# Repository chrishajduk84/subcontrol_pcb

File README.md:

# subcontrol_pcb
PCB for the subcontrol project

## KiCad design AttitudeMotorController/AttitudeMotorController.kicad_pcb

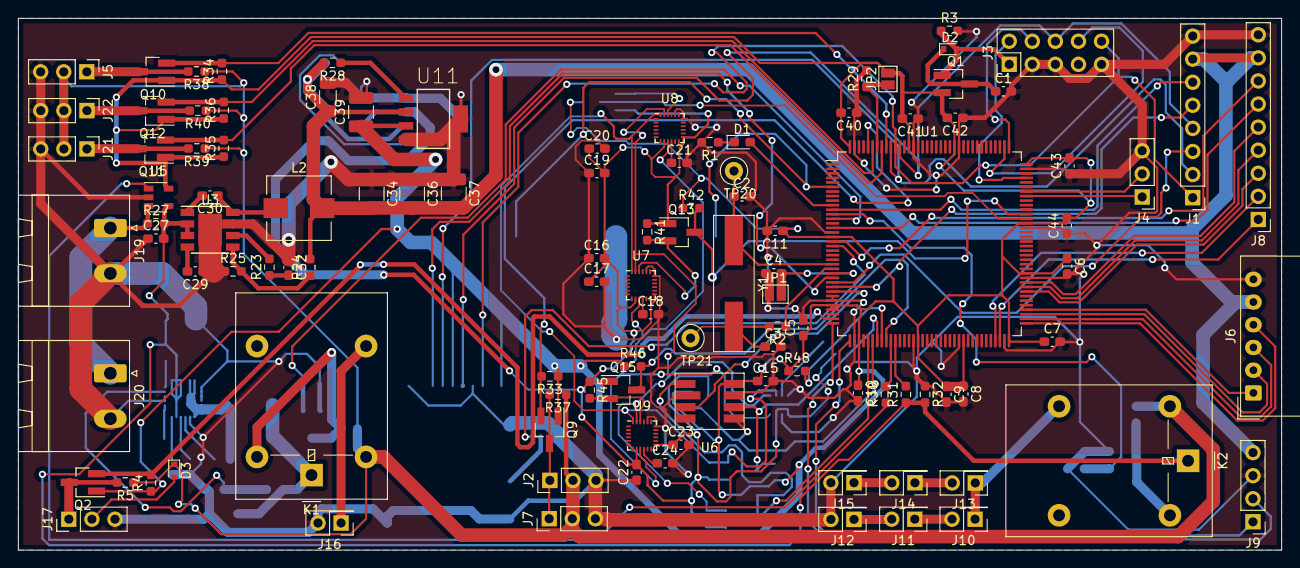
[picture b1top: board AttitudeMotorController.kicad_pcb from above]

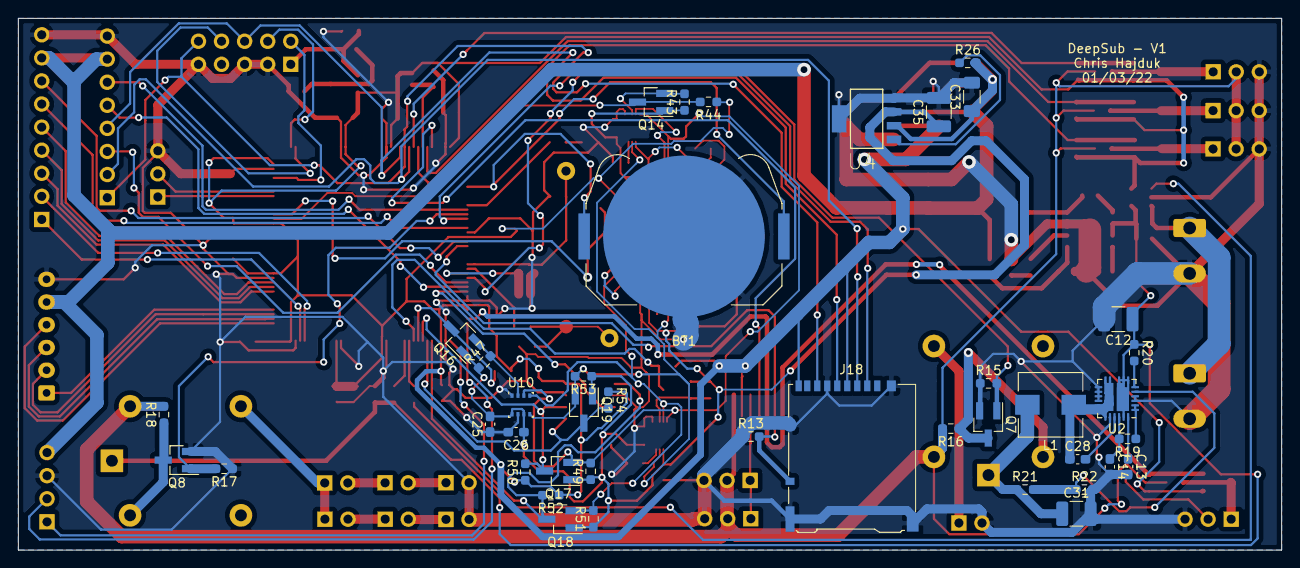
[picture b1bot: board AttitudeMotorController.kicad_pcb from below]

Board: 2 copper layers, 139.0 x 58.5 mm, 151 parts (41 on the bottom side), 101 nets.

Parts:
BT1: Battery_Cell; BatteryHolder_Keystone_3034_1x20mm
C1: 4.7uF; C_0603_1608Metric_Pad1.08x0.95mm_HandSolder
C2, C3: 50pF; C_0603_1608Metric_Pad1.08x0.95mm_HandSolder
C4, C5, C6, C7, C8, C9, C10, C11, C15, C16, C17, C18, C19, C20, C21, C22, C23, C24, C25, C26, C30, C40, C41, C42, C43, C44: 100nF; C_0603_1608Metric_Pad1.08x0.95mm_HandSolder
C12: 33uF X7R; C_1210_3225Metric_Pad1.33x2.70mm_HandSolder
C13, C14: 1uF; C_0603_1608Metric_Pad1.08x0.95mm_HandSolder
C27: 10uF; C_0603_1608Metric_Pad1.08x0.95mm_HandSolder
C28: 0.1uF; C_0603_1608Metric_Pad1.08x0.95mm_HandSolder
C29: 10nF; C_0603_1608Metric_Pad1.08x0.95mm_HandSolder
C31: 88uF X7R; C_1210_3225Metric_Pad1.33x2.70mm_HandSolder
C32: 2.7nF; C_0603_1608Metric_Pad1.08x0.95mm_HandSolder
C33, C38: 68uF; C_1206_3216Metric_Pad1.33x1.80mm_HandSolder
C34, C36, C37: 22uF; C_1210_3225Metric_Pad1.33x2.70mm_HandSolder
C35, C39: 33uF; C_1210_3225Metric_Pad1.33x2.70mm_HandSolder
D1: LED; LED_0603_1608Metric_Pad1.05x0.95mm_HandSolder
D2, D3: D_Schottky; D_SOD-523
J1: WIFI_Connector; PinHeader_1x08_P2.54mm_Vertical
J2, J7: EMERGENCY_BUOYANCY; PinHeader_1x03_P2.54mm_Vertical
J3: Conn_ARM_JTAG_SWD_10; PinHeader_2x05_P2.54mm_Vertical
J4: DEBUG_UART; PinHeader_1x03_P2.54mm_Vertical
J5: FLAP_TOP; PinHeader_1x03_P2.54mm_Vertical
J6: CAMERA_SPI; Molex_SPOX_5268-06A_1x06_P2.50mm_Horizontal
J8: LTE_Connector; PinHeader_1x09_P2.54mm_Vertical
J9: GPS_UART; PinHeader_1x04_P2.54mm_Vertical
J10: LED6; PinHeader_2x01_P2.54mm_Vertical
J11: LED5; PinHeader_2x01_P2.54mm_Vertical
J12: LED4; PinHeader_2x01_P2.54mm_Vertical
J13: LED3; PinHeader_2x01_P2.54mm_Vertical
J14: LED2; PinHeader_2x01_P2.54mm_Vertical
J15: LED1; PinHeader_2x01_P2.54mm_Vertical
J16: BUOYANCY; PinHeader_2x01_P2.54mm_Vertical
J17: Thrust_Out; PinHeader_1x03_P2.54mm_Vertical
J18: Micro_SD_Card_Det; microSD_HC_Hirose_DM3AT-SF-PEJM5
J19: PowerInput; PhoenixContact_MSTBA_2,5_2-G_1x02_P5.00mm_Horizontal
J20: ESC; PhoenixContact_MSTBA_2,5_2-G_1x02_P5.00mm_Horizontal
J21: FLAP_LEFT; PinHeader_1x03_P2.54mm_Vertical
J22: FLAP_RIGHT; PinHeader_1x03_P2.54mm_Vertical
JP1, JP2: Jumper_NO_Small; SolderJumper-2_P1.3mm_Open_Pad1.0x1.5mm
K1, K2: G5LE-1; Relay_SPDT_Omron-G5LE-1
L1: 1uH; L_Wuerth_HCI-7050
L2: 2.2uH; L_Wuerth_HCI-7050
Q1: Q_PMOS_GSD; SOT-23_Handsoldering
Q2, Q7, Q8, Q9, Q10, Q11, Q12, Q13, Q14, Q15, Q16, Q17, Q18, Q19: Q_NMOS_GSD; SOT-23_Handsoldering
R1: 130R; R_0603_1608Metric_Pad0.98x0.95mm_HandSolder
R2: 1.98K; R_0603_1608Metric_Pad0.98x0.95mm_HandSolder
R3, R4, R5, R13, R15, R16, R17, R18, R26, R28, R29, R30, R31, R33, R34, R35, R36, R37, R38, R39, R40: 10K; R_0603_1608Metric_Pad0.98x0.95mm_HandSolder
R19, R32: 100K; R_0603_1608Metric_Pad0.98x0.95mm_HandSolder
R20: 114k; R_0603_1608Metric_Pad0.98x0.95mm_HandSolder
R21: 2.5k; R_0603_1608Metric_Pad0.98x0.95mm_HandSolder
R22: 8k; R_0603_1608Metric_Pad0.98x0.95mm_HandSolder
R23: 5.62k; R_0603_1608Metric_Pad0.98x0.95mm_HandSolder
R24: 27.4k; R_0603_1608Metric_Pad0.98x0.95mm_HandSolder
R25: 22.1k; R_0603_1608Metric_Pad0.98x0.95mm_HandSolder
R27: 0.03R; R_0603_1608Metric_Pad0.98x0.95mm_HandSolder
R41, R42, R43, R44, R45, R46, R47, R48, R49, R50, R51, R52, R53, R54: 2.2K; R_0603_1608Metric_Pad0.98x0.95mm_HandSolder
TP20, TP21: TestPoint; TestPoint_Loop_D2.50mm_Drill1.0mm
U1: STM32F101ZETx; LQFP-144_20x20mm_P0.5mm
U2: AOZ2238QI-01
U3: AP64501; Diodes_SO-8EP
U4: LP3962EMP-1.8; SOT150P696X180-5N
U5: INA193; SOT-23-5
U6: MS5803-30BA
U7, U8, U9: ICM-20948; InvenSense_QFN-24_3x3mm_P0.4mm
U10: BME280; Bosch_LGA-8_2.5x2.5mm_P0.65mm_ClockwisePinNumbering
U11: LP3962EMP-3.3; SOT150P696X180-5N
Y1: Crystal 8MHz 10pF; Crystal_SMD_Wurtg-830011301-2Pin_9.6x4.1mm_HandSoldering

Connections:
+1V5: C31.1, K1.1, L1.2, R21.1
+1V8: C16.2, C17.1, C19.2, C20.1, C22.2, C23.1, C25.2, C26.1, C35.1, Q13.1, Q14.1, Q15.1, Q16.1, Q17.1, Q18.1, Q19.1, R41.1, R43.1, R45.1, R47.1, R49.1, R51.1, R53.1, U4.3, U7.8, U7.13, U8.8, U8.13, U9.8, U9.13, U10.6, U10.8
+3V3: C5.1, C6.1, C7.1, C8.1, C9.1, C10.1, C11.1, C15.1, C39.1, C40.2, C41.2, C42.2, C43.2, C44.2, J18.4, J18.9, JP2.2, Q1.2, Q2.1, Q9.1, Q10.1, Q11.1, Q12.1, R4.1, R33.1, R34.1, R35.1, R36.1, R42.1, R44.1, R46.1, R48.1, R50.1, R52.1, R54.1, U1.17, U1.32, U1.33, U1.39, U1.52, U1.62, U1.72, U1.84, U1.95, U1.108, U1.121, U1.131, U1.144, U5.5, U6.5, U11.3
+3V8: C33.1, C34.2, C36.2, C37.2, C38.1, J1.7, J6.5, J8.8, J9.4, L2.2, R24.2, R26.2, R28.2, U4.2, U11.2
+5V: D3.1, J2.2, J5.2, J7.2, J21.2, J22.2, K1.2, K2.2, R5.1, R16.2, R18.2, R37.1, R38.1, R39.1, R40.1
+BATT: BT1.1, U1.6
/BuoyancyTanks/OUTPUT: J16.1, K1.3
/LEDs/OUTPUT: J10.1, J13.1, K2.3
/sensors/LevelShifter/Signal2: Q13.2, R41.2, U7.22
/sensors/MISO_1.8: Q19.2, R53.2, U7.9, U8.9, U9.9, U10.5
/sensors/MOSI_1.8: Q17.2, R49.2, U7.24, U8.24, U9.24, U10.3
/sensors/SCK_1.8: Q18.2, R51.2, U7.23, U8.23, U9.23, U10.4
/sensors/sheet625E3AF9/Signal2: Q14.2, R43.2, U8.22
/sensors/sheet625E4E06/Signal2: Q16.2, R47.2, U10.2
/sensors/sheet625E4524/Signal2: Q15.2, R45.2, U9.22
BuoyancyEnable: Q7.1, R15.2, U1.13
CARD_DETECT: J18.10, R13.2, U1.19
DTR: J8.5, U1.82
FLAP_LEFT: Q11.2, R35.2, U1.137
FLAP_RIGHT: Q12.2, R36.2, U1.139
FLAP_TOP: Q10.2, R34.2, U1.136
GND: BT1.2, C1.2, C2.2, C3.2, C4.1, C5.2, C6.2, C7.2, C8.2, C9.2, C10.2, C11.2, C12.2, C13.2, C14.2, C15.2, C16.1, C17.2, C18.2, C19.1, C20.2, C21.2, C22.1, C23.2, C24.2, C25.1, C26.2, C27.1, C29.1, C31.2, C32.1, C33.2, C34.1, C35.2, C36.1, C37.1, C38.2, C39.2, C40.1, C41.1, C42.1, C43.1, C44.1, J1.8, J2.3, J3.3, J3.5, J3.9, J4.3, J5.3, J6.6, J7.3, J8.9, J9.3, J12.2, J15.2, J16.2, J17.3, J18.6, J18.11, J19.2, J20.2, J21.3, J22.3, JP1.1, Q7.2, Q8.2, R1.2, R3.2, R13.1, R15.1, R17.1, R22.2, R25.1, R29.2, R32.1, U1.16, U1.30, U1.31, U1.38, U1.51, U1.61, U1.71, U1.83, U1.94, U1.107, U1.120, U1.130, U1.143, U2.3, U2.4, U2.12, U2.13, U2.14, U2.15, U2.19, U3.7, U3.8, U4.4, U4.5, U5.2, U6.2, U6.6, U7.18, U7.20, U8.18, U8.20, U9.18, U9.20, U10.1, U10.7, U11.4, U11.5
JTDI: J3.8, U1.110
JTDO-TRACESWO: J1.4, J3.6, J18.5, U1.133
JTRST: J1.1, J3.10, J18.7, U1.134
LED_ON: Q8.1, R17.2, U1.12
LTE_STATUS: J8.7, U1.18
unnamed: C4.2, JP1.2, U1.25
unnamed: C13.1, U2.23
unnamed: C14.1, R19.2, U2.21
unnamed: C18.1, U7.10
unnamed: C21.1, U8.10
unnamed: C24.1, U9.10
unnamed: C28.1, L1.1, U2.10, U2.11, U2.16, U2.17, U2.18
unnamed: C28.2, U2.20
unnamed: C29.2, U3.4
unnamed: C30.1, L2.1, U3.8
unnamed: C30.2, U3.1
unnamed: C32.2, R23.1
unnamed: D1.1, R1.1
unnamed: D1.2, U1.10
unnamed: D2.2, J3.1, Q1.1, R3.1
unnamed: D3.2, J17.2
unnamed: J2.1, J7.1, Q9.3, R37.2
unnamed: J5.1, Q10.3, R38.2
unnamed: J10.2, J11.1
unnamed: J11.2, J12.1
unnamed: J13.2, J14.1
unnamed: J14.2, J15.1
unnamed: J17.1, Q2.3, R5.2
unnamed: J19.1, J20.1, R27.1, U5.3
unnamed: J21.1, Q11.3, R39.2
unnamed: J22.1, Q12.3, R40.2
unnamed: JP2.1, R29.1, U1.138
unnamed: K1.5, Q7.3, R16.1
unnamed: K2.5, Q8.3, R18.1
unnamed: R2.1, U1.24
unnamed: R19.1, U2.1, U2.2
unnamed: R20.2, U2.6
unnamed: R21.2, R22.1, U2.5
unnamed: R23.2, U3.6
unnamed: R24.1, R25.2, U3.5
unnamed: R26.1, U4.1
unnamed: R28.1, U11.1
unnamed: R30.2, U1.46
unnamed: R31.2, U1.47
OSC_IN: C2.1, TP20.1, U1.23, Y1.1
OSC_OUT: C3.1, R2.2, TP21.1, Y1.2
POWER_ON_LTE: J8.6, U1.15
PSUCurrent: R30.1, U5.1
PSUVoltage: C12.1, C27.2, K2.1, R20.1, R27.2, R31.1, R32.2, U2.7, U2.8, U2.9, U2.22, U3.2, U3.3, U5.4
SERVO_OUT: Q9.2, R33.2, U1.140
SPI1_CS1: Q13.3, R42.2, U1.97
SPI1_CS2: Q14.3, R44.2, U1.96
SPI1_CS3: Q15.3, R46.2, U1.45
SPI1_CS4: Q16.3, R48.2, U1.44
SPI1_CS5: U1.29, U6.3
SPI1_MISO: Q19.3, R54.2, U1.42, U6.8
SPI1_MOSI: Q17.3, R50.2, U1.43, U6.7
SPI1_SCK: Q18.3, R52.2, U1.41, U6.1
SPI2_MISO: J6.2, U1.75
SPI2_MOSI: J6.1, U1.76
SPI2_NSS: J6.4, U1.73
SPI2_SCK: J6.3, U1.74
SPI3_CS1: J18.2, U1.26
SPI3_CS2: J1.3, U1.27
SPI3_MOSI: J1.2, J18.3, U1.135
SPI3_NOTIFY: J1.5, U1.28
SWCLK-JTCK: J3.4, U1.109
SWDIO-JTMS: J3.2, U1.105
ThrustOut: Q2.2, R4.2, U1.35
UART1_RX: J4.2, U1.102
UART1_TX: J4.1, U1.101
UART2_RX: J9.1, U1.37
UART2_TX: J9.2, U1.36
UART3_CTS: J8.3, U1.80
UART3_RTS_DE: J8.4, U1.81
UART3_RX: J8.1, U1.70
UART3_TX: J8.2, U1.69
VDD: C1.1, D2.1, Q1.3
WIFI_SLEEP: J1.6, U1.11

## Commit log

2023-12-20 Initial PCB commit
